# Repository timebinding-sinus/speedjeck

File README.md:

# speedjeck
PCB board based on arduino nano, keyboard emulator, password manager

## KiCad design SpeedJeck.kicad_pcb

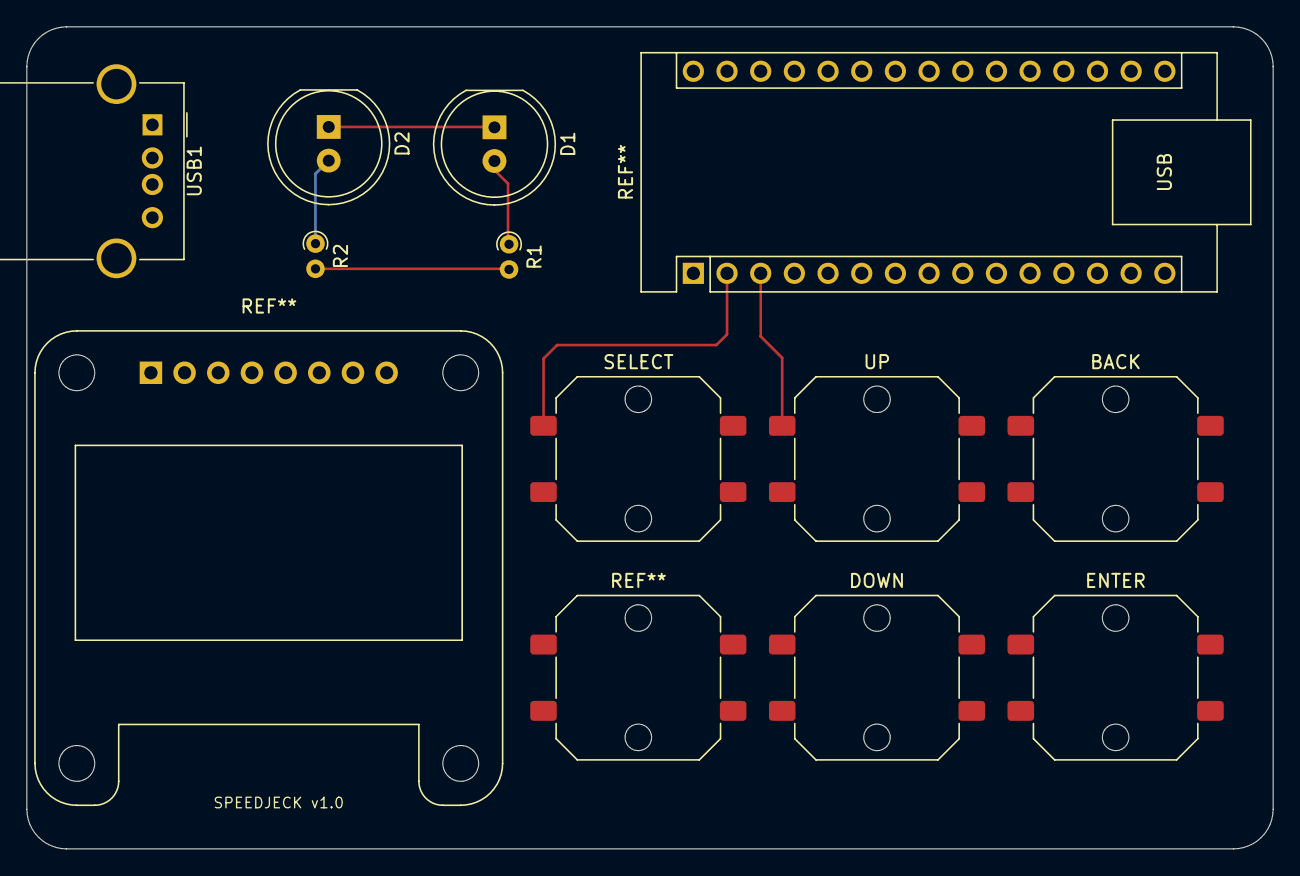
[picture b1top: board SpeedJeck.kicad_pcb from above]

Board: 2 copper layers, 94.0 x 62.0 mm, 10 parts (0 on the bottom side), 4 nets.

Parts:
BACK: SW_Push_1P1T_NO_CK_PTS125Sx43PSMTR
D1, D2: LED; LED_D8.0mm
DOWN: SW_Push_1P1T_NO_CK_PTS125Sx43PSMTR
ENTER: SW_Push_1P1T_NO_CK_PTS125Sx43PSMTR
R1, R2: 2K5; R_Axial_DIN0204_L3.6mm_D1.6mm_P1.90mm_Vertical
SELECT: SW_Push_1P1T_NO_CK_PTS125Sx43PSMTR
UP: SW_Push_1P1T_NO_CK_PTS125Sx43PSMTR
USB1: USB_A_Molex_67643_Horizontal

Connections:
+5V: R1.2, R2.2
GND: D1.1 (K), D2.1 (K)
unnamed: D1.2 (A), R1.1
unnamed: D2.2 (A), R2.1

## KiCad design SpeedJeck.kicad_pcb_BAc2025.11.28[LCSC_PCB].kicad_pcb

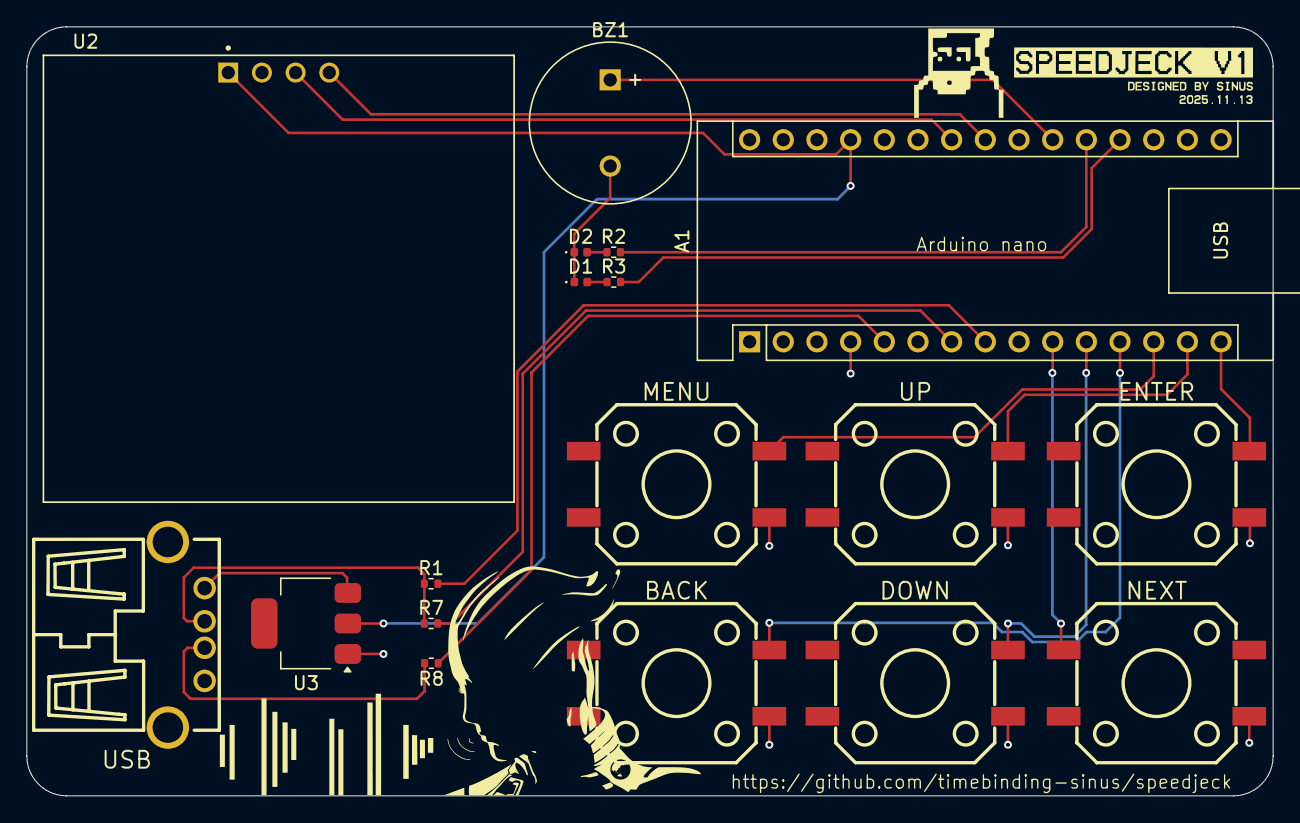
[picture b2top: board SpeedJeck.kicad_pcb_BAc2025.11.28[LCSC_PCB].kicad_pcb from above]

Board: 2 copper layers, 94.0 x 58.0 mm, 18 parts (0 on the bottom side), 21 nets.

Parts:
A1: Arduino_Nano_v3.x; Arduino_Nano
BACK: SW_Push; SW-SMD_4P-L12.0-W12.0-P5.00-LS15.2
BZ1: Buzzer; MagneticBuzzer_ProSignal_ABT-410-RC
D1, D2: LED; LED_0402_1005Metric
DOWN: SW_Push; SW-SMD_4P-L12.0-W12.0-P5.00-LS15.2
ENTER: SW_Push; SW-SMD_4P-L12.0-W12.0-P5.00-LS15.2
MENU: SW_Push; SW-SMD_4P-L12.0-W12.0-P5.00-LS15.2
NEXT: SW_Push; SW-SMD_4P-L12.0-W12.0-P5.00-LS15.2
R1: 2K2; R_0402_1005Metric
R2, R3: 1K; R_0402_1005Metric
R7, R8: 68; R_0402_1005Metric
U2: Adafruit SSD1306 1.3 inch; LCD_OLED_128X64_1.3_I2C
U3: AMS1117-3.3; SOT-223-3_TabPin2
UP: SW_Push; SW-SMD_4P-L12.0-W12.0-P5.00-LS15.2
USB: USB_A; USB-A-TH_USB-M-1_C2346

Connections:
+3.3V: A1.27 (+5V), U2.1 (Vcc), U3.2 (VO)
/Data+: R8.2, USB.3 (D+)
/Data-: R1.1, R7.1, USB.2 (D-)
A0: A1.19 (A0), R3.2
A1: A1.20 (A1), R2.2
A2: A1.21 (A2), BZ1.1 (+)
A4: A1.23 (A4), U2.4 (SDA)
A5: A1.24 (A5), U2.3 (SCK)
D2: A1.5 (D2), R8.1
D4: A1.7 (D4), R7.2
D5: A1.8 (D5), R1.2
D7: A1.10 (D7), NEXT.1
D8: A1.11 (D8), DOWN.2
D9: A1.12 (D9), BACK.2
D10: A1.13 (D10), MENU.2
D11: A1.14 (D11), UP.2
D12: A1.15 (D12), ENTER.2
GND: A1.4 (GND), BACK.2, BZ1.2 (-), D1.1 (K), D2.1 (K), DOWN.2, ENTER.2, MENU.2, NEXT.2, U2.2 (GND), U3.1 (GND), UP.2, USB.4 (GND)
unnamed: D1.2 (A), R3.1
unnamed: D2.2 (A), R2.1
unnamed: U3.3 (VI), USB.1 (VBUS)

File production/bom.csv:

Designator,Footprint,Quantity,Value,LCSC Part #
A1,Arduino_Nano,1,Arduino_Nano_v3.x,
"BACK, DOWN, MENU, NEXT, OK, UP",SW_Push_1P1T_NO_CK_PTS125Sx73SMTR,6,SW_Push,
BZ1,MagneticBuzzer_ProSignal_ABT-410-RC,1,Buzzer,
"D1, D2",0402,2,LED,
J1,USB_A_TE_292303-7_Horizontal,1,USB_A,
R1,0402,1,2K2,
"R2, R3",0402,2,1K,
"R7, R8",0402,2,68,
U1,LCD_OLED_128X64_1.3_I2C,1,Adafruit SSD1306 1.3 inch,
U2,SOT-223-3_TabPin2,1,AMS1117-3.3,

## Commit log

2025-11-02 [schEMATIC] [VERSION CODE 1v] [Ref 1] [02.11.2025]
2025-11-13 [schEMATIC] [VERSION CODE 1v] [Ref 2], [PCB] [version code 1] [rev 1] [13.11.2025] [Final SPEEDJECK 1v]
2025-11-28 [MANUFACTURE] [LCSC components] [JLCPCB] [version code 1] [28.11.2025] [SPEEDJECK 1v]
2025-12-01 [Replacement a component 2k2] [MANUFACTURE] [LCSC components] [JLCPCB] [version code 1] [01.12.2025] [SPEEDJECK 1v]
